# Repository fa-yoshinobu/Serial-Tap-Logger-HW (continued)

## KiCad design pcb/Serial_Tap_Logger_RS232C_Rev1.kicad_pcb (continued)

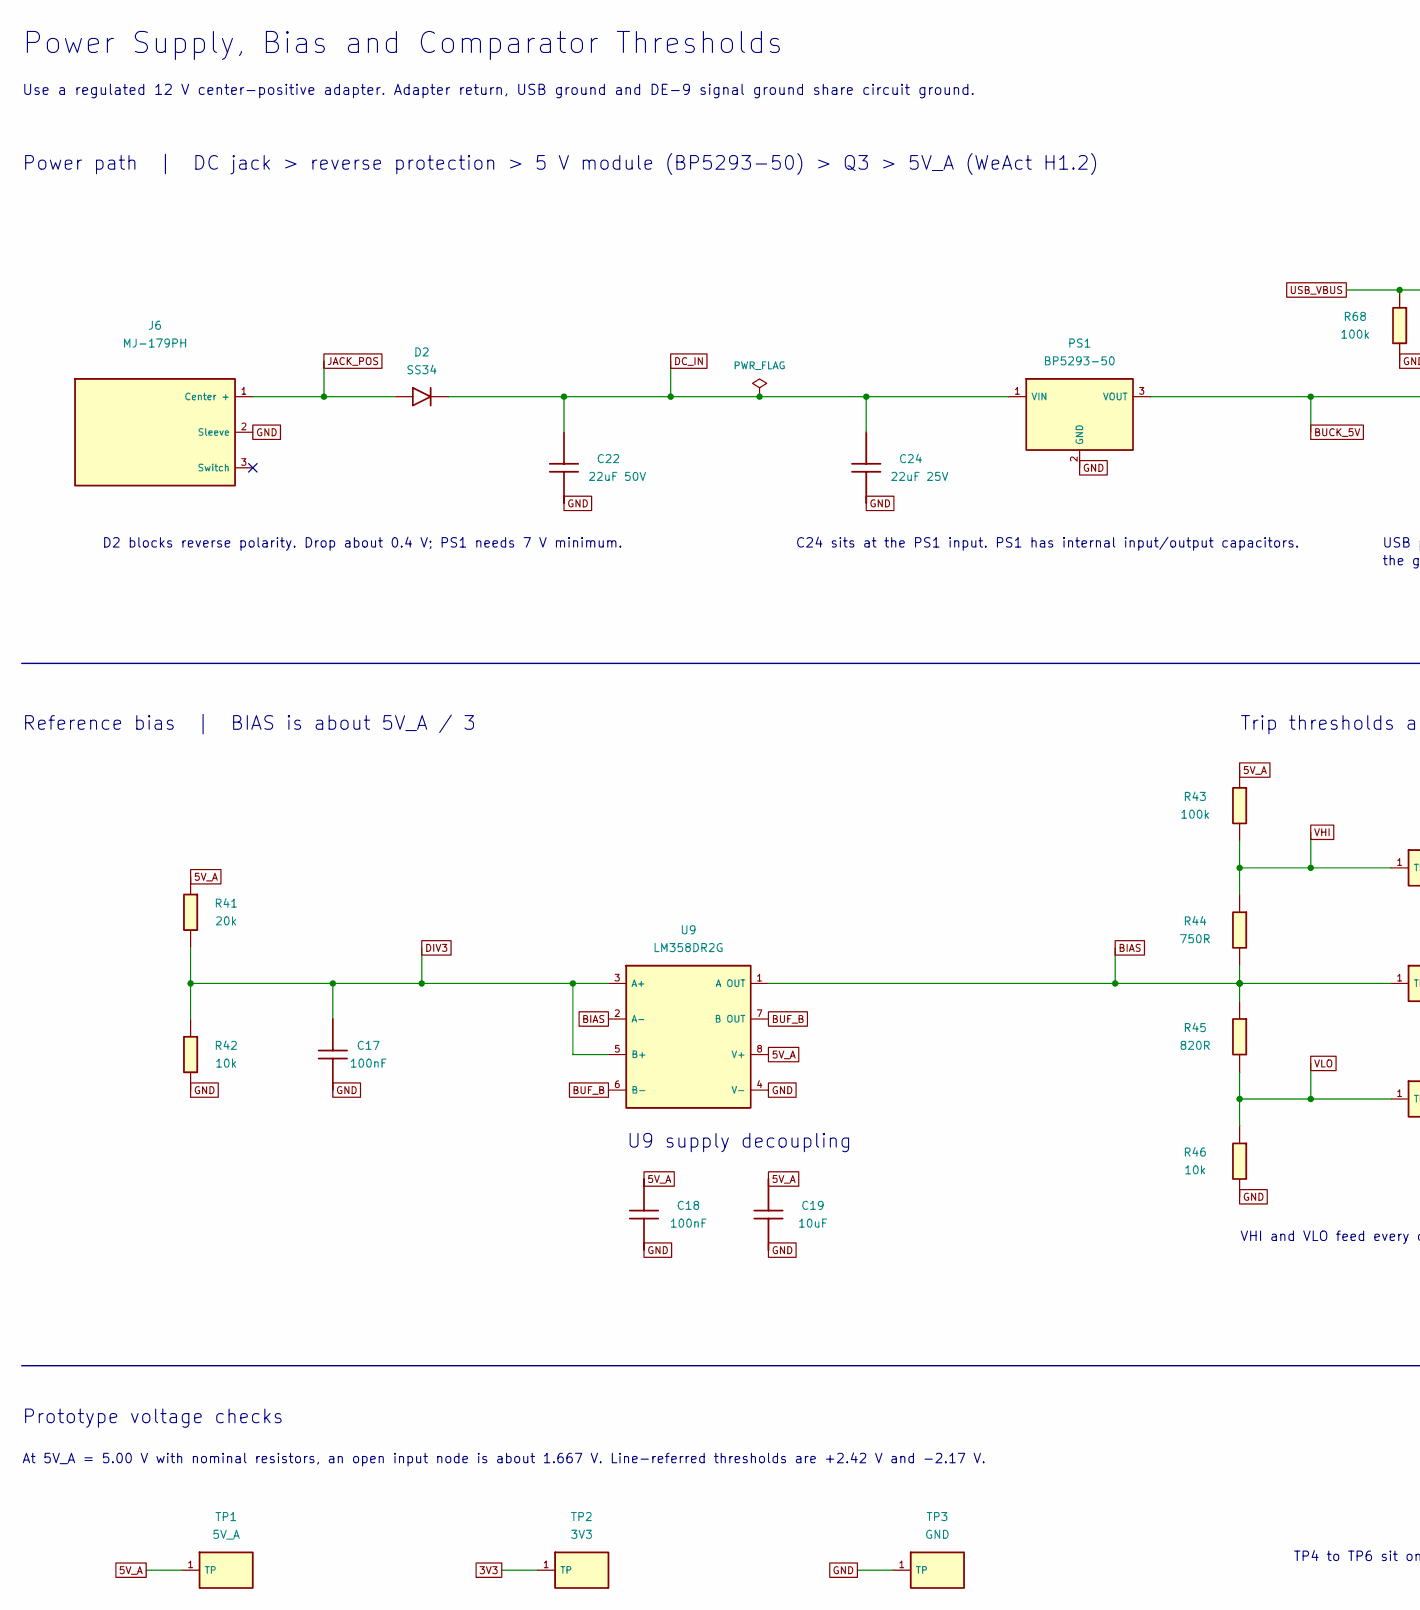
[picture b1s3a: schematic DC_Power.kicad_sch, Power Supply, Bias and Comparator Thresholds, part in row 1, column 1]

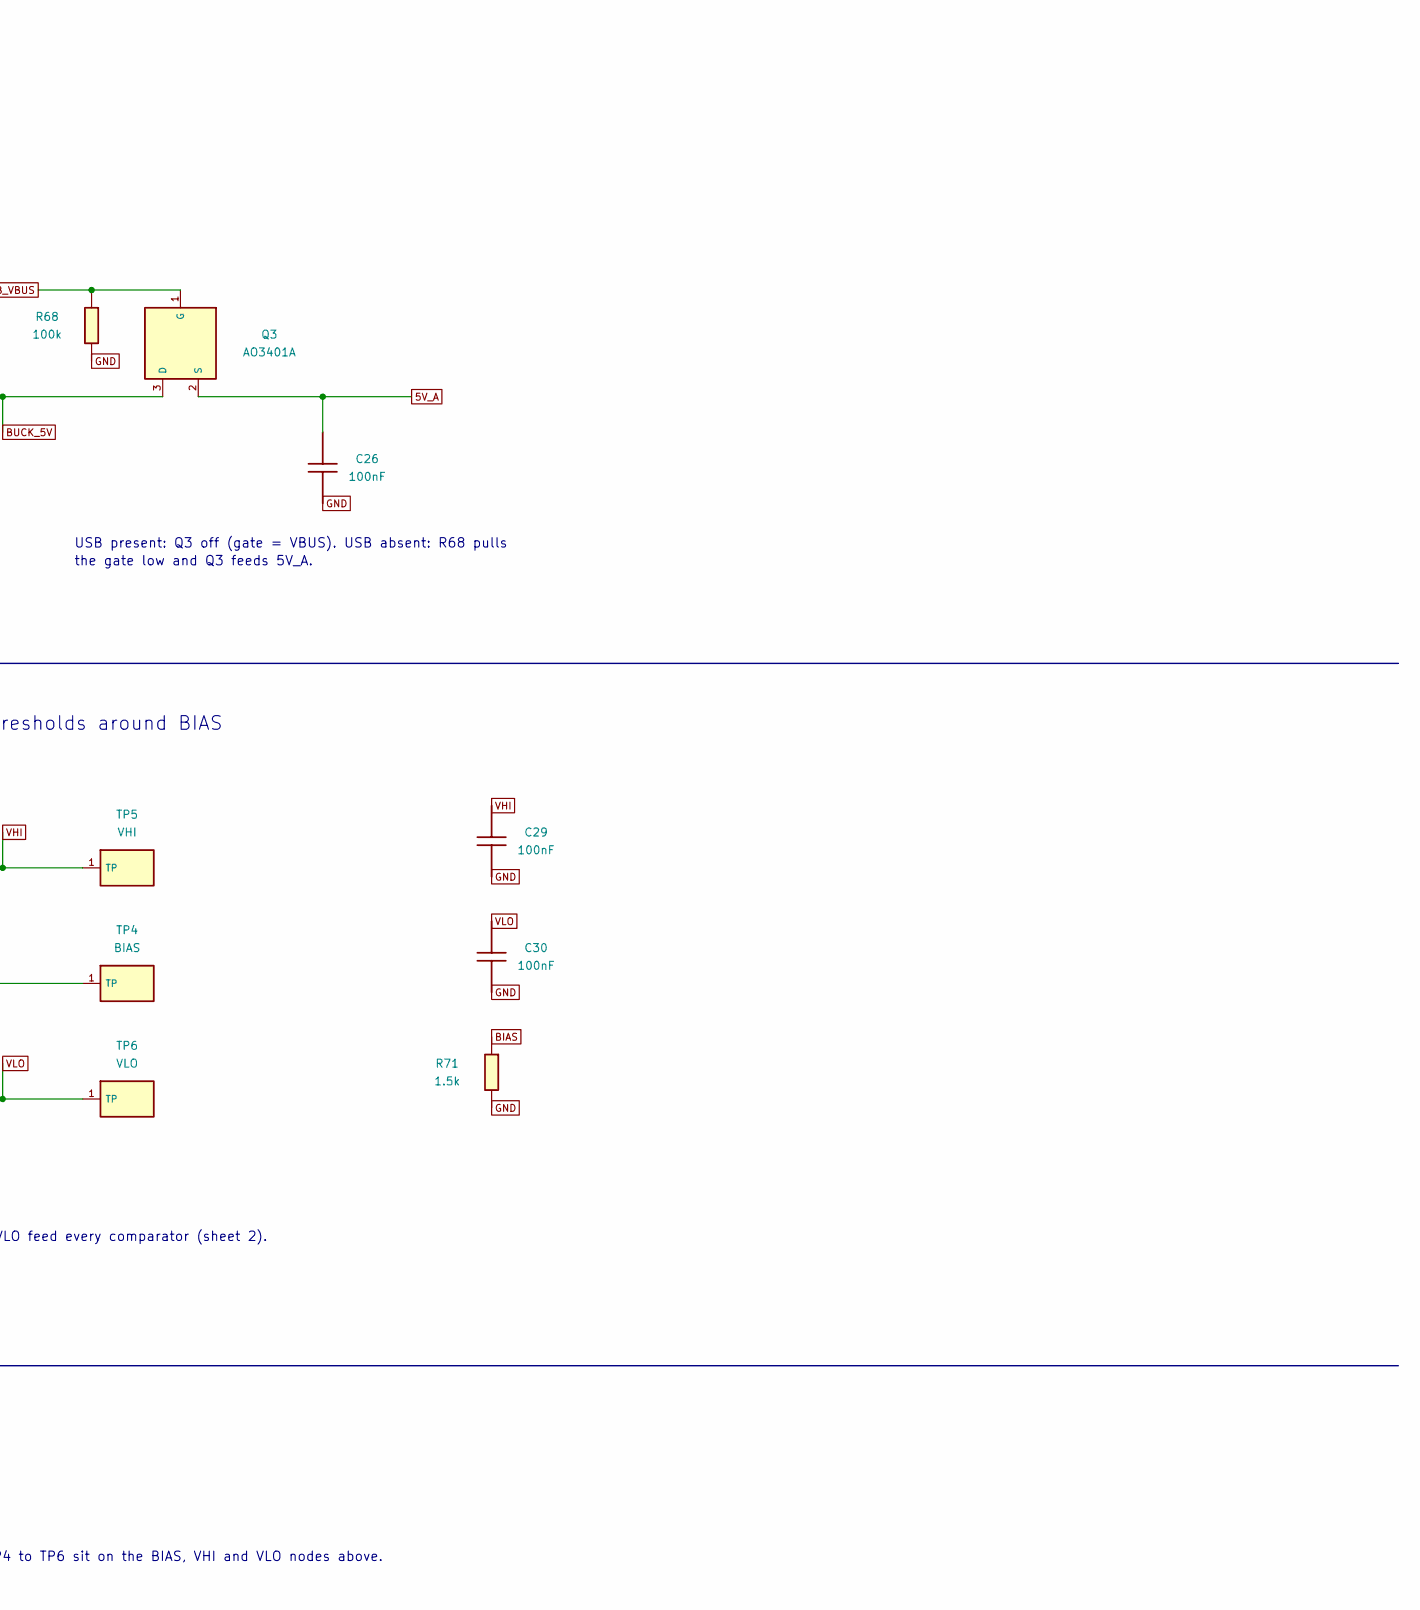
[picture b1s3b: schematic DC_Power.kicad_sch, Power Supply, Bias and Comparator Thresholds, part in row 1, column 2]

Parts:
C17, C18, C26, C29, C30: 100nF; C_0603_1608Metric_DFM; MPN CC0603KRX7R9BB104; LCSC C14663
C19: 10uF; C_0805_2012Metric_DFM; MPN CL21A106KAYNNNE; LCSC C15850
C22: 22uF 50V; Murata_RDE_108156_Horizontal_P5mm; MPN RDEC71H226MWK1H03B
C24: 22uF 25V; C_1206_3216Metric_DFM; MPN CL31A226KAHNNNE; LCSC C12891
D2: SS34; D_SMA_DFM; MPN SS34; LCSC C8678
J6: MJ-179PH; MJ179PH_BoardEdge; MPN MJ-179PH
PS1: BP5293-50; ROHM_BP5293_SIP3; MPN BP5293-50
Q3: AO3401A; SOT-23_DFM; MPN AO3401A; LCSC C15127
R41: 20k; R_0603_1608Metric_DFM; MPN 0603WAF2002T5E; LCSC C4184
R42, R46: 10k; R_0603_1608Metric_DFM; MPN 0603WAF1002T5E; LCSC C25804
R43, R68: 100k; R_0603_1608Metric_DFM; MPN 0603WAF1003T5E; LCSC C25803
R44: 750R; R_0603_1608Metric_DFM; MPN 0603WAF7500T5E; LCSC C23241
R45: 820R; R_0603_1608Metric_DFM; MPN 0603WAF8200T5E; LCSC C23253
R71: 1.5k; R_0603_1608Metric_DFM; MPN 0603WAF1501T5E; LCSC C22843
TP1: 5V_A; TestPoint_Pad_D1.5mm_DFM
TP2: 3V3; TestPoint_Pad_D1.5mm_DFM
TP3: GND; TestPoint_Pad_D1.5mm_DFM
TP4: BIAS; TestPoint_Pad_D1.5mm_DFM
TP5: VHI; TestPoint_Pad_D1.5mm_DFM
TP6: VLO; TestPoint_Pad_D1.5mm_DFM
U9: LM358DR2G; SOIC-8_3.9x4.9mm_P1.27mm_DFM; MPN LM358DR2G; LCSC C7950

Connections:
3V3: TP2.1 (TP_1); also elsewhere on the board
5V_A: C18.1, C19.1, C26.1, Q3.2 (S), R41.1, R43.1, TP1.1 (TP_1), U9.8 (V+); also elsewhere on the board
BIAS: R44.2, R45.1, R71.1, TP4.1 (TP_1), U9.1 (A_OUT), U9.2 (A-); also elsewhere on the board
BUCK_5V: PS1.3 (VOUT), Q3.3 (D)
BUF_B: U9.6 (B-), U9.7 (B_OUT)
DC_IN: C22.1, C24.1, D2.1 (K), PS1.1 (VIN)
DIV3: C17.1, R41.2, R42.1, U9.3 (A+), U9.5 (B+)
GND: C17.2, C18.2, C19.2, C22.2, C24.2, C26.2, C29.2, C30.2, J6.2 (Sleeve), PS1.2 (GND), R42.2, R46.2, R68.2, R71.2, TP3.1 (TP_1), U9.4 (V-); also elsewhere on the board
JACK_POS: D2.2 (A), J6.1 (Center_+)
USB_VBUS: Q3.1 (G), R68.1; also elsewhere on the board
VHI: C29.1, R43.2, R44.1, TP5.1 (TP_1); also elsewhere on the board
VLO: C30.1, R45.2, R46.1, TP6.1 (TP_1); also elsewhere on the board

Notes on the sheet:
Power Supply, Bias and Comparator Thresholds
Use a regulated 12 V center-positive adapter. Adapter return, USB ground and DE-9 signal ground share circuit ground.
Power path | DC jack > reverse protection > 5 V module (BP5293-50) > Q3 > 5V_A (WeAct H1.2)
D2 blocks reverse polarity. Drop about 0.4 V; PS1 needs 7 V minimum.
C24 sits at the PS1 input. PS1 has internal input/output capacitors.
USB present: Q3 off (gate = VBUS). USB absent: R68 pulls
the gate low and Q3 feeds 5V_A.
Reference bias | BIAS is about 5V_A / 3
Trip thresholds around BIAS
VHI and VLO feed every comparator (sheet 2).
U9 supply decoupling
Prototype voltage checks
At 5V_A = 5.00 V with nominal resistors, an open input node is about 1.667 V. Line-referred thresholds are +2.42 V and -2.17 V.
TP4 to TP6 sit on the BIAS, VHI and VLO nodes above.

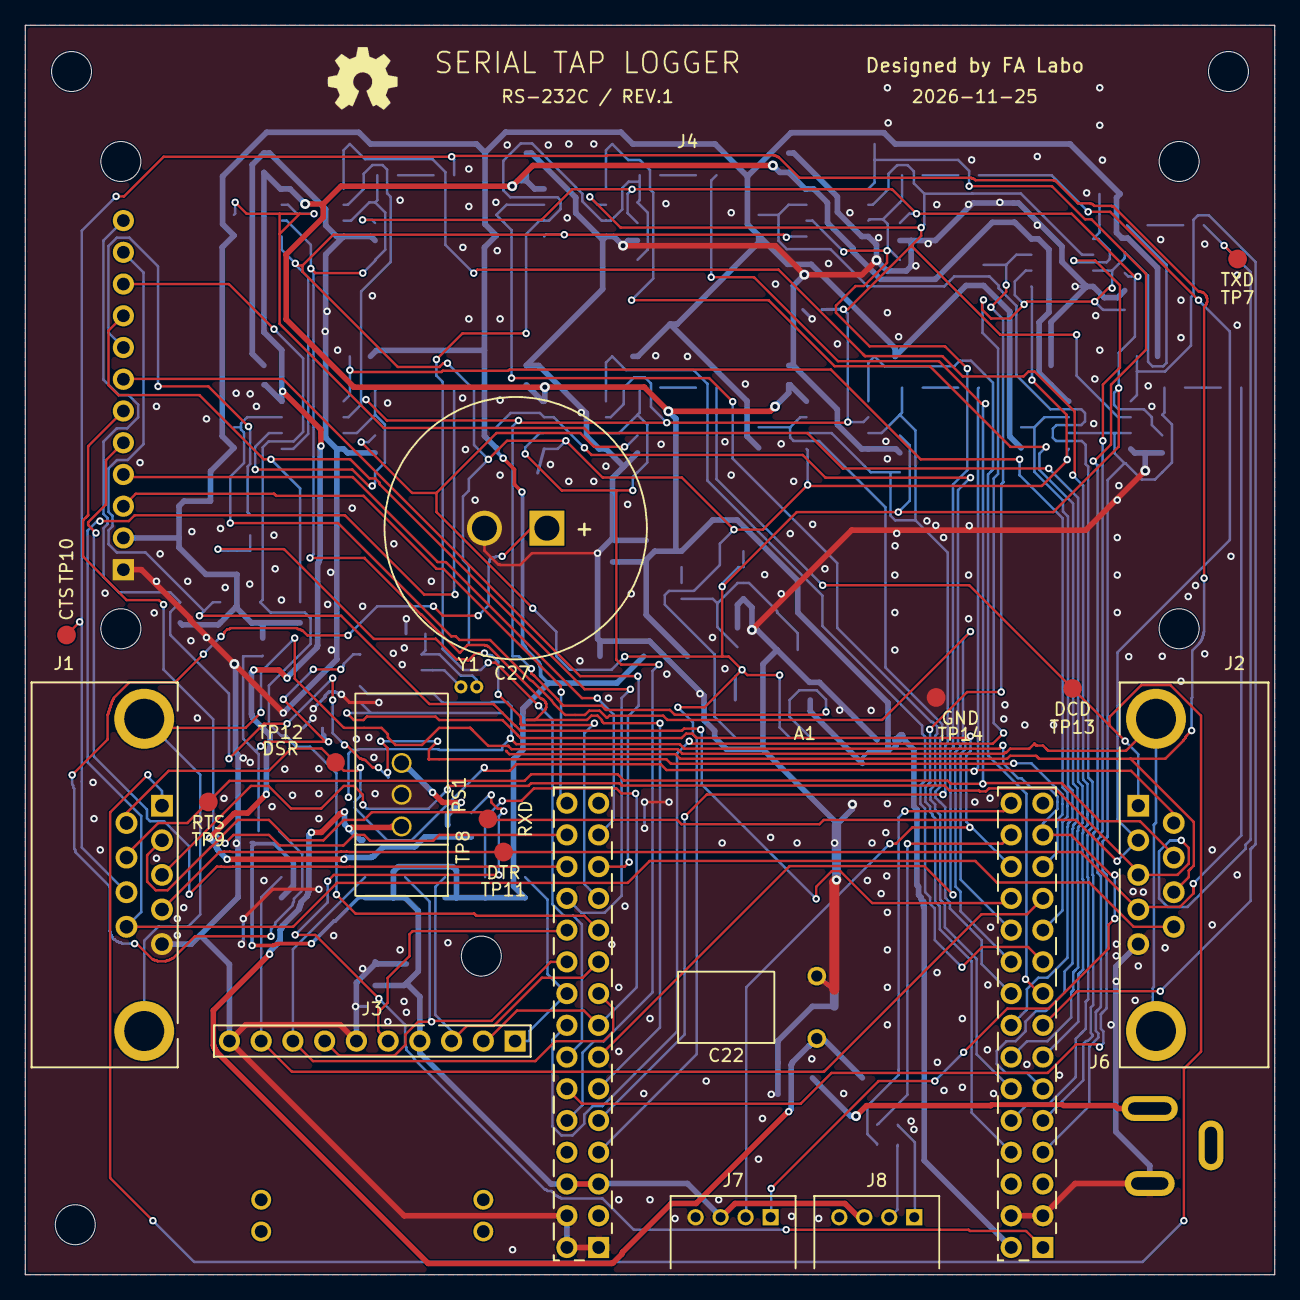
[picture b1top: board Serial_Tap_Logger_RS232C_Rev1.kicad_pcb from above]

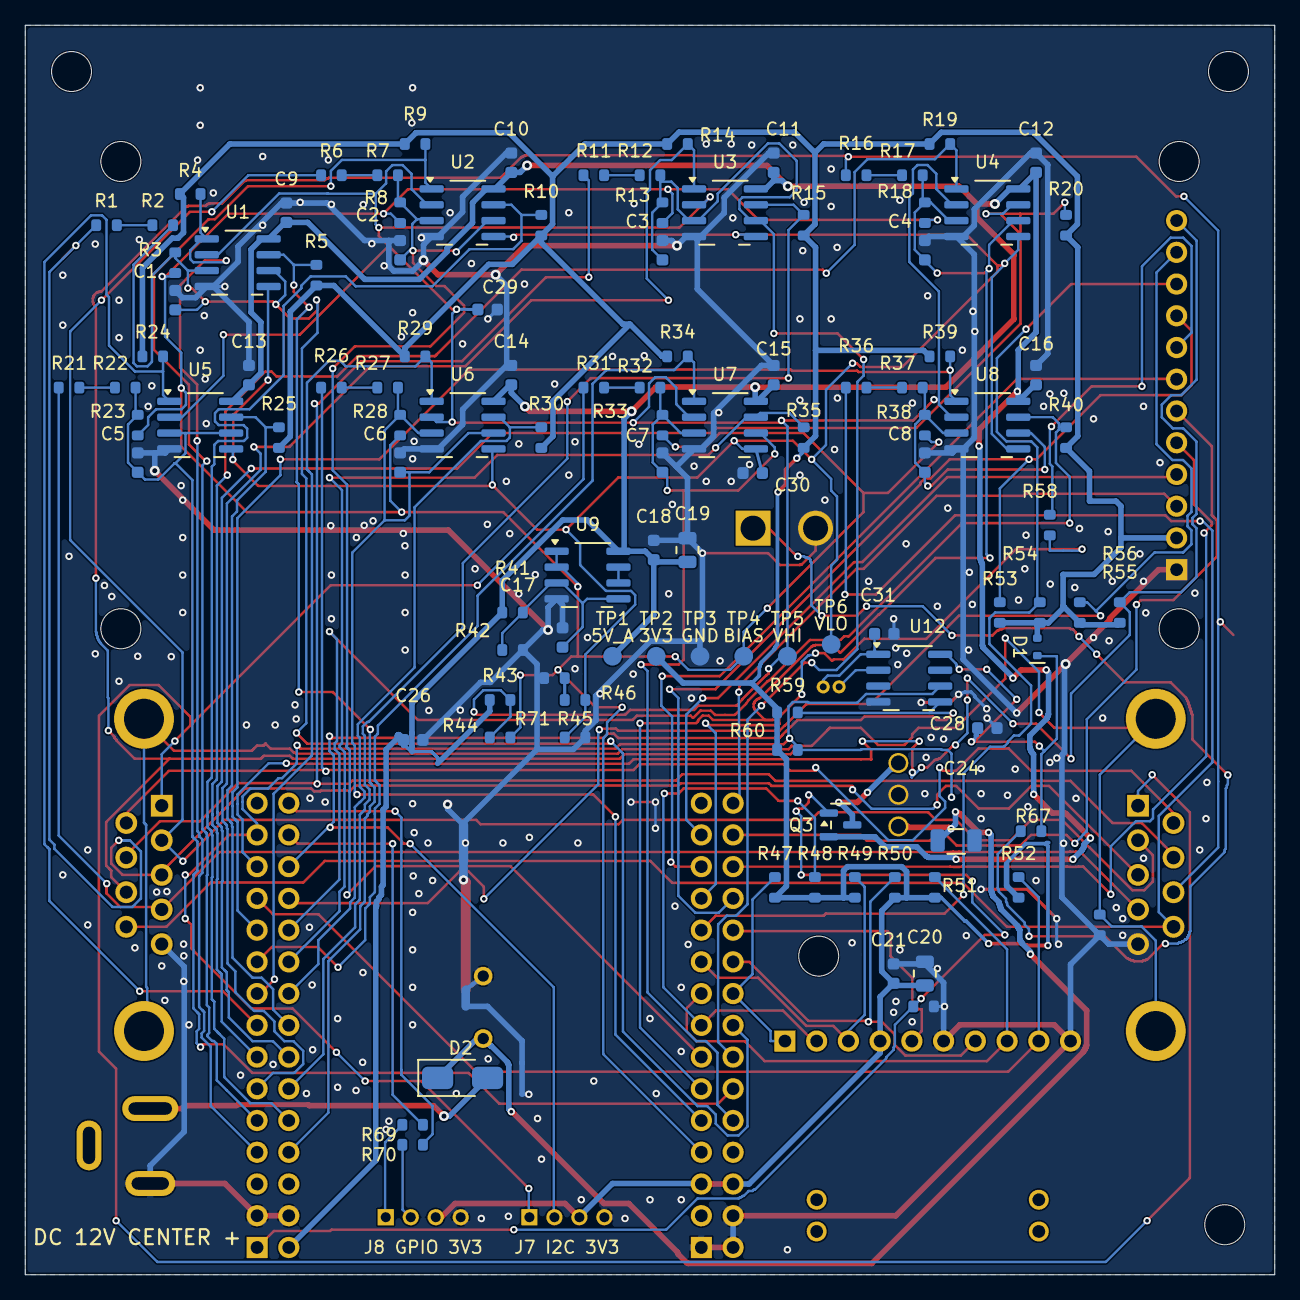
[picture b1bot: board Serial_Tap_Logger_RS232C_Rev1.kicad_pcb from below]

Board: 2 copper layers, 100.0 x 100.0 mm, 136 parts (115 on the bottom side), 81 nets.

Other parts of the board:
H1, H2, H3, H4: M3; MountingHole_3.2mm_M3
LOGO1: OSHW-Symbol_5.6x5mm_SilkScreen

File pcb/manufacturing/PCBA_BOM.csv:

Comment,Designator,Footprint,LCSC Part #,Quantity,Value
CL10C101JB8NNNC,"C1,C2,C3,C4,C5,C6,C7,C8",C_0603_1608Metric,C14858,8,100pF
CL10C220JB8NNNC,C31,C_0603_1608Metric,C1653,1,22pF
CC0603KRX7R9BB104,"C9,C10,C11,C12,C13,C14,C15,C16,C17,C18,C21,C26,C28,C29,C30",C_0603_1608Metric,C14663,15,100nF
CL21A106KAYNNNE,"C19,C20",C_0805_2012Metric,C15850,2,10uF
CL31A226KAHNNNE,C24,C_1206_3216Metric,C12891,1,22uF 25V
SS34,D2,D_SMA,C8678,1,SS34
BAT54X,D1,D_SOD-523,C19627026,1,BAT54X
AO3401A,Q3,SOT-23,C15127,1,AO3401A
0603WAF1003T5E,"R1,R2,R6,R7,R11,R12,R16,R17,R21,R22,R26,R27,R31,R32,R36,R37,R43,R68",R_0603_1608Metric,C25803,18,100k
0603WAF6801T5E,"R3,R8,R13,R18,R23,R28,R33,R38",R_0603_1608Metric,C23212,8,6.8k
0603WAF1002T5E,"R4,R5,R9,R10,R14,R15,R19,R20,R24,R25,R29,R30,R34,R35,R39,R40,R42,R46,R47,R48,R49,R50,R51,R52,R53,R54,R55,R56",R_0603_1608Metric,C25804,28,10k
0603WAF3301T5E,"R59,R60",R_0603_1608Metric,C22978,2,3.3k
0603WAF2002T5E,R41,R_0603_1608Metric,C4184,1,20k
0603WAF7500T5E,R44,R_0603_1608Metric,C23241,1,750R
0603WAF8200T5E,R45,R_0603_1608Metric,C23253,1,820R
0603WAF1001T5E,R67,R_0603_1608Metric,C21190,1,1k
0603WAF1000T5E,"R69,R70",R_0603_1608Metric,C22775,2,100R
0603WAF100JT5E,R58,R_0603_1608Metric,C22859,1,10R
LM393DR2G,"U1,U2,U3,U4,U5,U6,U7,U8",SOIC-8_3.9x4.9mm_P1.27mm,C7955,8,LM393DR2G
LM358DR2G,U9,SOIC-8_3.9x4.9mm_P1.27mm,C7950,1,LM358DR2G
"PCF8563T/5,518",U12,SOIC-8_3.9x4.9mm_P1.27mm,C7440,1,PCF8563T
0603WAF1501T5E,R71,R_0603_1608Metric,C22843,1,1.5k
